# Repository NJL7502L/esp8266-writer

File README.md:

# esp8266-writer

Arduinoからesp-01に書き込む。bigsurがch340gとまだうまくいってないようなので。

esp8266-writerというよりesp01-writerだな。

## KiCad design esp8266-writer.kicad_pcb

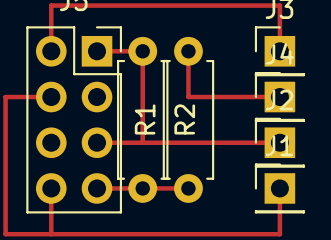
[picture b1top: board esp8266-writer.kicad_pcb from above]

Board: 2 copper layers, 7 parts (0 on the bottom side), 5 nets.

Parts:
J1: Arduino3v3; PinHeader_1x01_P2.54mm_Vertical
J2: ArduinoGND; PinHeader_1x01_P2.54mm_Vertical
J3: ArduinoTxD; PinHeader_1x01_P2.54mm_Vertical
J4: ArduinoRxD; PinHeader_1x01_P2.54mm_Vertical
J5: esp8266_conn; PinSocket_2x04_P2.54mm_Vertical
R1: 1k; R_Axial_DIN0207_L6.3mm_D2.5mm_P7.62mm_Horizontal
R2: 2.2k; R_Axial_DIN0207_L6.3mm_D2.5mm_P7.62mm_Horizontal

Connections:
+3V3: J1.1, J5.4, J5.8
GND: J2.1, J5.1, J5.5, R2.1
unnamed: J4.1, R1.2
Rx: J5.7, R1.1, R2.2
Tx: J3.1, J5.2

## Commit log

2020-12-28 zsh init: rename files
2020-12-28 zsh init: add submodule kicad
2020-12-28 zsh init: add submodule digikey
2020-12-28 zsh init: edit sym-lib-table digikey
2020-12-28 zsh init: edit readme
2020-12-28 zsh init: rm init
2020-12-28 回路を引いた
2020-12-28 フットプリントの割当、ネットリストの生成
2020-12-28 配線した
2020-12-28 img追加
